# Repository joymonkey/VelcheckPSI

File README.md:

# Velcheck PSI Reproduction Project

**PSI** : Process State Indicator, the round color light seen on R2-D2's dome (one blue/red in front, one yellow/green in rear)

**Velcheck** : Pioneering member of the R2 Builders Club, 80's synth virtuoso

In the early days of the R2 Builders, Mike Velcheck designed and supplied a PSI for club members around the world. His design has been the basis for most PSI's since, all sharing the same footprint, many with an abundance of LEDs and fancy swipe animations, none as simple and plug-n-play friendly as Mikes. In December of 2021 Mike passed away.

This project aims to bring back Mike Velcheck's great PSI design, so that it may continue to make its way into droids. Using a donor unit, I reverse clumgeneered Mike's PCB, making a couple of very minor tweaks to the layout. An unused capacitor was removed, in it's place is a powerful Devo Energy Dome (a nod to Mike's involvement with RadioStar Band). The resulting Eagle PCB and schematic files are found within this repository, along with gerber files for production, firmware .bin and Mike's own instruction manual.

**Usage** 

See Mike's PDF user guide in this repository.

**Through-Hole Assembly**

The boards come partially assembled, but the through-hole components will need to be soldered in place. Before starting, you should decide on your LED layout (see Checkerboard vs Side by Side beloe).

 * Being mindful of polarity and color placement, each LED can then be soldered in place.
 * Next, you'll want to solder the 8-pin IC socket, which the PIC MCU (U1) will eventually sit in.
 * Solder the jumper pins for JP1 and JP2.
 * Solder the 2-pin and 4-pin screw terminals.
 * Carefully insert the pre-programmed PIC MCU into its socket.

To test, apply 12V to the 2-pin screw terminal (being mindful of polarity). 

**Checkerboard vs Side by Side?**

By moving two resistors on the board, it can be configured with LEDs in a checkerboard layout (giving a better 'spead' of each color), or side-by-side layout (which allows the PSI to appear 'stuck' with both red and blue lit at the same time). The board uses 220 ohm ressitors to limit current to each branch of 3 LEDs. For checkerboard layout, R9 and R10 should not be populated. For side-by-side layout, R8 and R5 should not be populated.

**Using with JEDI Displays**

The PIC IC can be removed, and two wires run from a JEDI Display controller. This allows the JEDI Display to set the PSI's to their specific colors (useful during animations) rather than the onboard PIC.

**Bill Of Materials**

The kit should coime will all parts needed, but if you'd like to build from scratch, here is a BOM for all parts. For LEDs, high brightness and 120 degree viewing angle is recommended. For standard R2-D2 colors, you'll need 6 red, 6 blue, 6 yellow, 6 green. In the US, SuperBrightLEDs sell suitable 5m LEDs for about 50c each. These offer better spread of color than typical cheap 5mm LEDs.

 * U1 : PIC10F202-I/P 8-bit MCU (typically in an )
 * U2 : AS78L05RTR-E1 5V LDO
 * C2 : 330nf 50V 0805 X7R capacitor
 * C3 : 100nf 50V 0805 X7R capacitor
 * R1, R2 : 10K ohm 0603 resistor
 * R3, R6 : 3.3K ohm 0603 resistor
 * R4, R5, R7, R8 : 220 ohm 0603 resistor
 * D1-D12 : 5mm LEDs, various colors
 * D13 : 1N4001 diode
 * Q1, Q2 : MBT2222A BJT NPN transistor
 * P1 : 2-pin 2.54mm pitch screw terminal
 * P2 : 4-pin 2.54mm pitch screw terminal
 * JP1 & JP2 : 2.54mm 2-row 2-column male pin header

**Firmware**

The firmware .bin file in this repository was copied directly from one of Mike's PSI's. Unfortunately source code is unavailable. To program a blank PIC IC, you'll need a programmer such as a PicKit3.

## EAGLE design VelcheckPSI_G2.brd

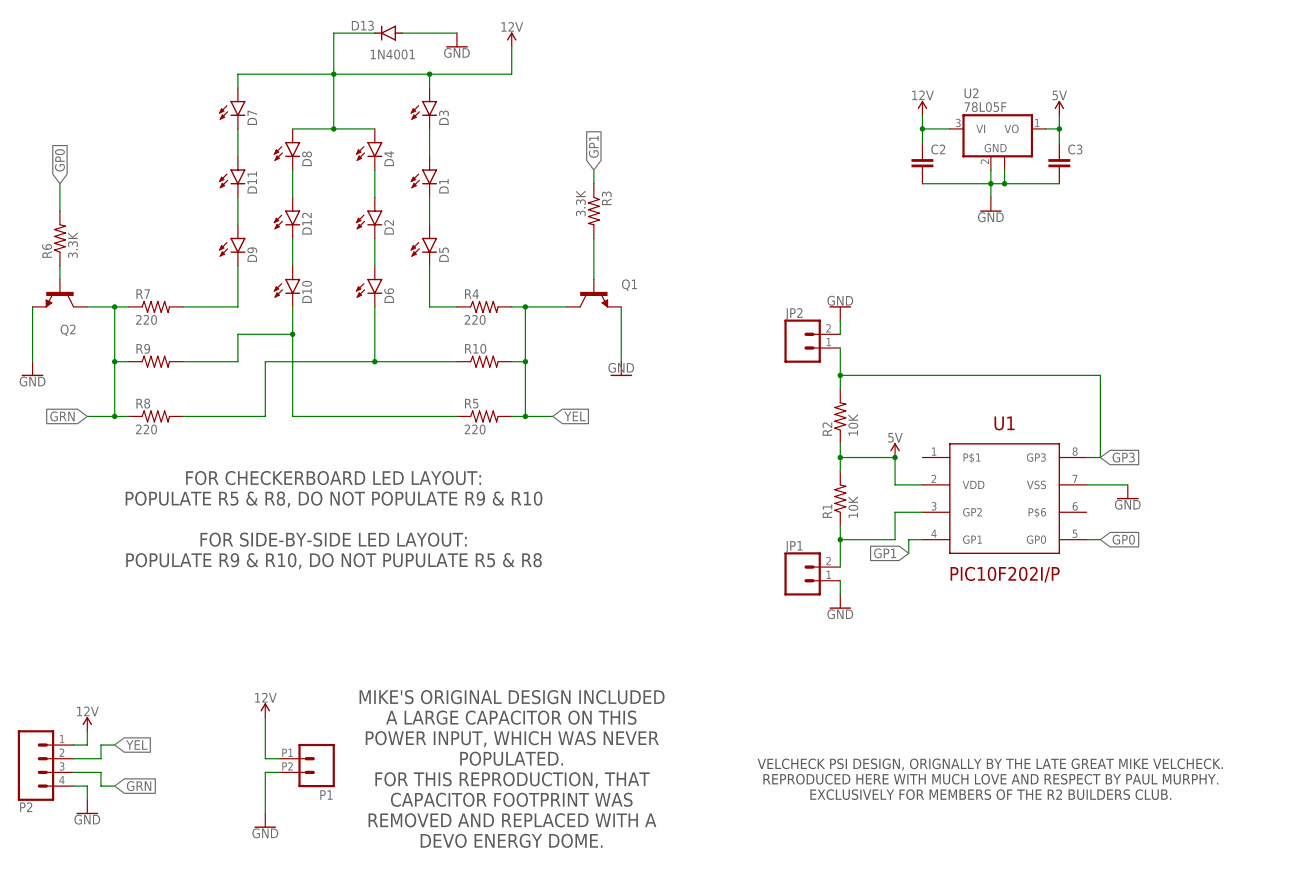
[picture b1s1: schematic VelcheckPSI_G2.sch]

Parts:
C2, C3: C-EUC0805; C0805
D1, D2, D3, D4, D5, D6, D7, D8, D9, D10, D11, D12: LED5MM; LED5MM_SLIM
D13: 1N4001; DO-214AC
JP1, JP2: CONN_02; 1X02
P1: M022.54MM_SCREWTERM; 1X02_2.54_SCREWTERM
P2: CONN_04POLAR; MOLEX-1X4
Q1, Q2: MMBT2222ALT1-NPN-SOT23-BEC; SOT23-BEC
R1, R2: 10K; R0603
R3, R6: 3.3K; R0603
R4, R5, R7, R8: 220; R0603
R9, R10: R-US_R0603; R0603
U1: PIC10F202I/P; DIP762W53P254L949H508Q8B
U2: 78L05F; SOT89

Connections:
5V: C3.1, R1.2, R2.1, U1.2 (VDD), U2.1 (VO)
12V: C2.1, D3.A, D4.A, D7.A, D8.A, D13.C, P1.P1 (1), P2.1, U2.3 (VI)
GND: C2.2, C3.2, D13.A, JP1.1, JP2.2, P1.P2 (2), P2.4, Q1.E, Q2.E, U1.7 (VSS), U2.2 (GND), U2.2@1 (GND)
GP0: R6.2, U1.5 (GP0)
GP1: R3.1, U1.4 (GP1)
GP3: JP2.1, R2.2, U1.8 (GP3)
GRN: P2.3, Q2.C, R7.1, R8.1, R9.1
unnamed: Q2.B, R6.1
unnamed: Q1.B, R3.2
unnamed: JP1.2, R1.1, U1.3 (GP2)
unnamed: D5.K (C), R4.1
unnamed: D9.K (C), R7.2
unnamed: D10.K (C), R5.1, R9.2
unnamed: D1.A, D3.K (C)
unnamed: D2.A, D4.K (C)
unnamed: D1.K (C), D5.A
unnamed: D2.K (C), D6.A
unnamed: D6.K (C), R8.2, R10.1
unnamed: D7.K (C), D11.A
unnamed: D9.A, D11.K (C)
unnamed: D8.K (C), D12.A
unnamed: D10.A, D12.K (C)
YEL: P2.2, Q1.C, R4.2, R5.2, R10.2

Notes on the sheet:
FOR CHECKERBOARD LED LAYOUT: POPULATE R5 & R8, DO NOT POPULATE R9 & R10 FOR SIDE-BY-SIDE LED LAYOUT: POPULATE R9 & R10, DO NOT PUPULATE R5 & R8
MIKE'S ORIGINAL DESIGN INCLUDED A LARGE CAPACITOR ON THIS POWER INPUT, WHICH WAS NEVER POPULATED. FOR THIS REPRODUCTION, THAT CAPACITOR FOOTPRINT WAS REMOVED AND REPLACED WITH A DEVO ENERGY DOME.
VELCHECK PSI DESIGN, ORIGNALLY BY THE LATE GREAT MIKE VELCHECK. REPRODUCED HERE WITH MUCH LOVE AND RESPECT BY PAUL MURPHY. EXCLUSIVELY FOR MEMBERS OF THE R2 BUILDERS CLUB.

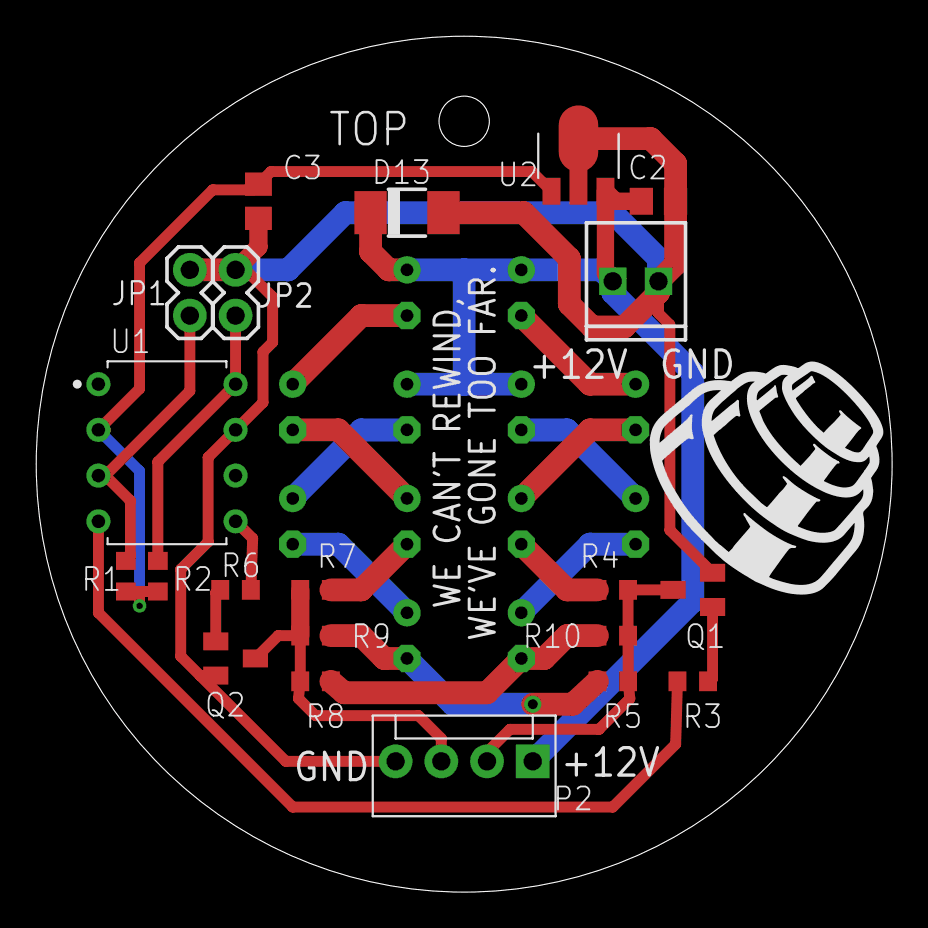
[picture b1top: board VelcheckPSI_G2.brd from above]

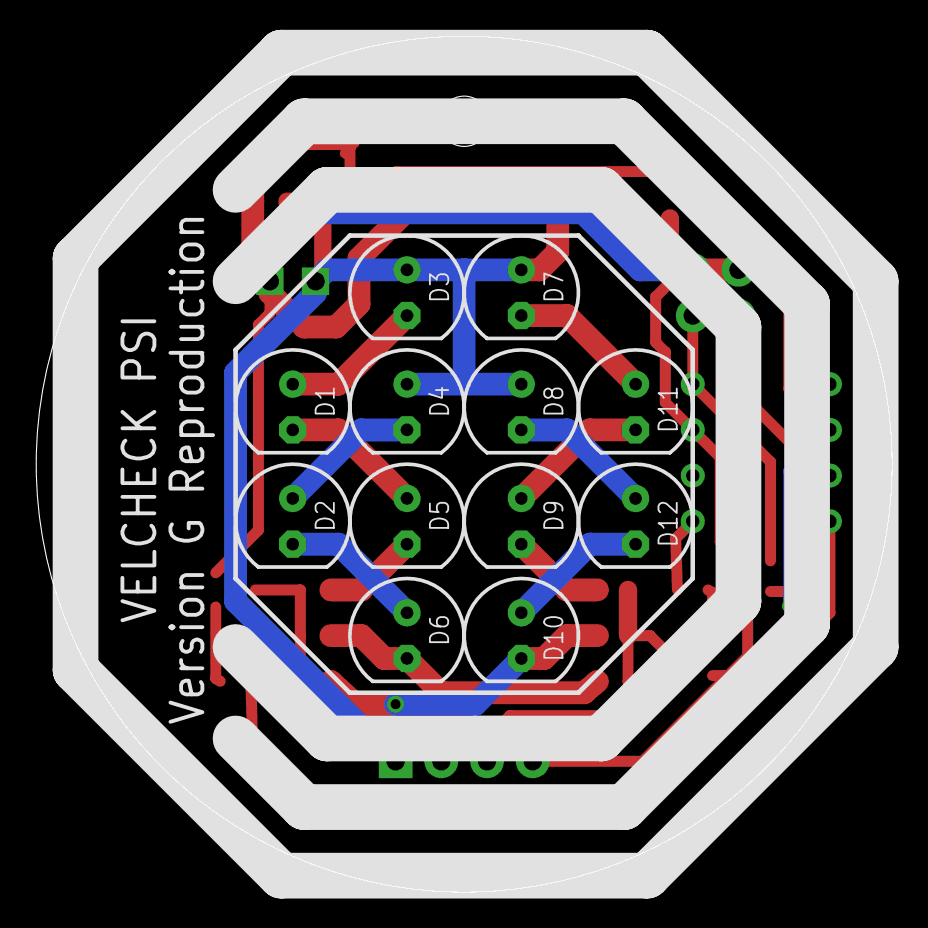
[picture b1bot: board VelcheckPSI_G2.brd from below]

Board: 2 copper layers, 47.5 x 47.5 mm, 34 parts (12 on the bottom side), 23 nets.

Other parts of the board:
U$1: DEVO

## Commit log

2022-05-03 Added my Eagle design files, gerbers & Mike's doc

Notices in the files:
parts and their libraries:
SparkFun-Connectors: Licensing: Creative Commons ShareAlike 4.0 International - https://creativecommons.org/licenses/by-sa/4.0
